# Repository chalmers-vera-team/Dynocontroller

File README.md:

# dynocontroller
Controller PCB for dyno. 

## Hardware
PCB created in Eagle 9.3.1
It is a shield to Arduino Uno that controls the dyno. 

## Software 
Software created in PlatformIO - VS Code.

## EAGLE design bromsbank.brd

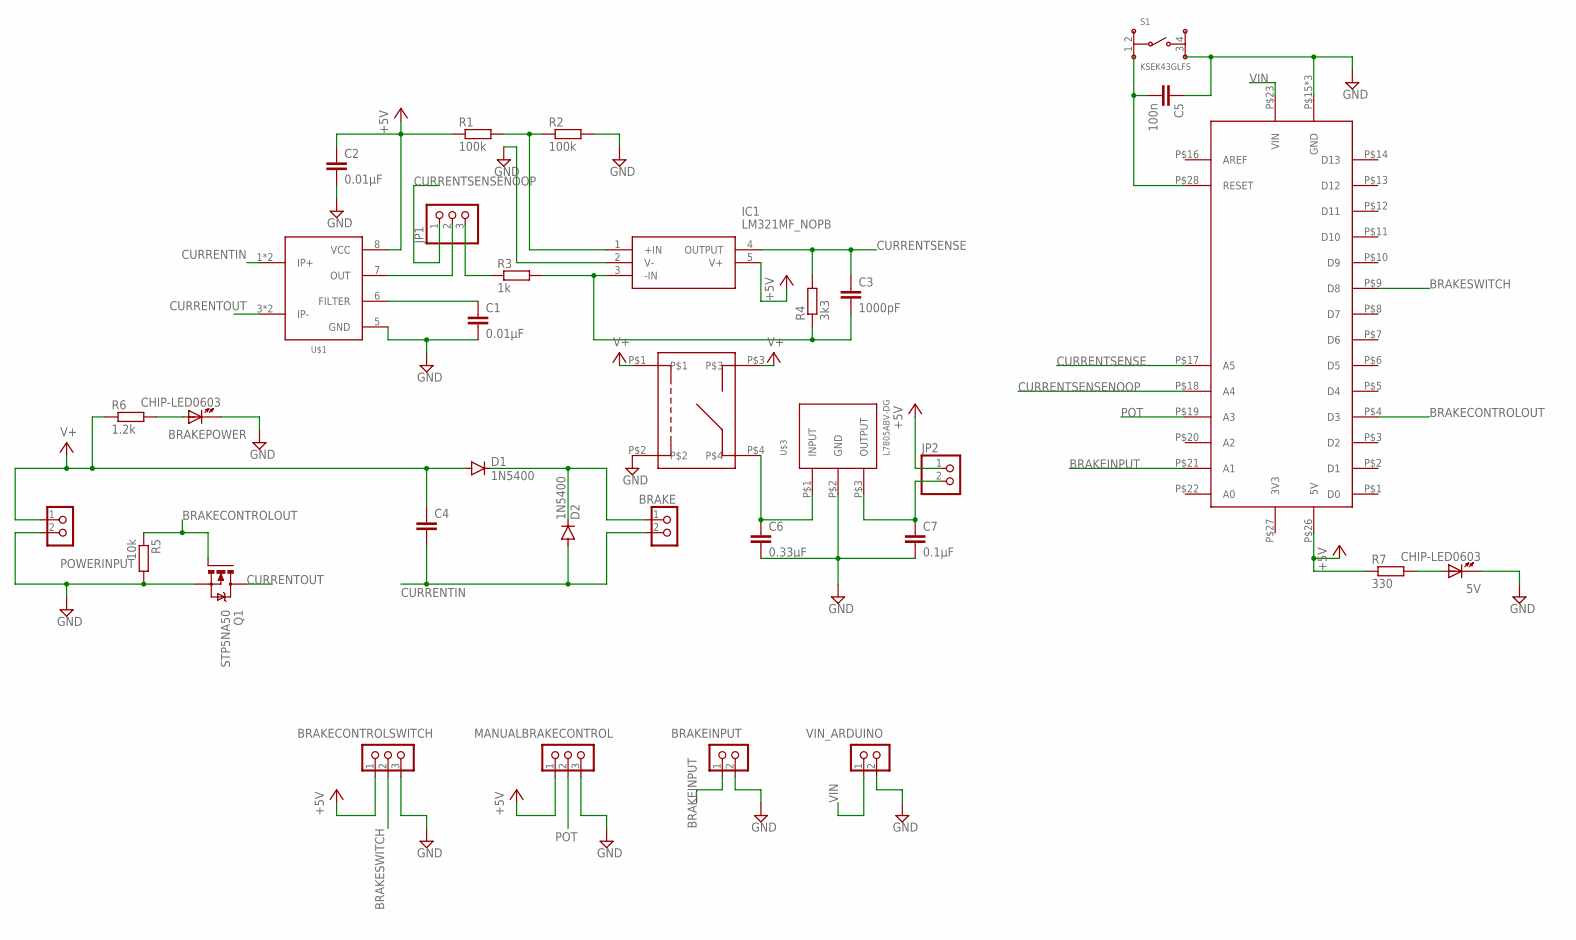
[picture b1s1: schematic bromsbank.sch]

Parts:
5V: CHIP-LED0603
BRAKE: EH_B2B-EH; B2B-EH
BRAKECONTROLSWITCH: EH_B3B-EH; B3B-EH
BRAKEINPUT: EH_B2B-EH; B2B-EH
BRAKEPOWER: CHIP-LED0603
C1, C2: 0.01µF; C0603
C3: 1000pF; C0603
C4: C-EU075-063X106; C075-063X106
C5: 100n; C0603
C6: 0.33µF; C0603
C7: 0.1µF; C0603
D1, D2: 1N5400; DO201-15
IC1: LM321MF_NOPB; SOT95P280X145-5N
JP1: PINHD-1X3; 1X03
JP2: PINHD-1X2; 1X02
MANUALBRAKECONTROL: EH_B3B-EH; B3B-EH
POWERINPUT: EH_B2B-EH; B2B-EH
Q1: STP5NA50; TO220BV
R1, R2: 100k; R0603
R3: 1k; R0603
R4: 3k3; R0603
R5: 10k; R0603
R6: 1.2k; R0603
R7: 330; R0603
S1: KSEK43GLFS
U$1: ACS712ELCTR-05B-T; SO08
U$2: ARDUINO_SHIELD; ARDUINO_UNO_SHIELD
U$3: L7805ABV-DG; TO-220
U$4: RELAY_SDT-S-124DMR,601; SDT-S-124DMR
VIN_ARDUINO: EH_B2B-EH; B2B-EH

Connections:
3V3: U$2.P$27 (3V3)
+5V: BRAKECONTROLSWITCH.1, C2.1, IC1.5 (V+), JP2.1, MANUALBRAKECONTROL.1, R1.1, R7.1, U$1.8 (VCC), U$2.P$26 (5V)
BRAKECONTROLOUT: Q1.G, R5.1, U$2.P$4 (D3)
BRAKEINPUT: BRAKEINPUT.1, U$2.P$21 (A1)
BRAKESWITCH: BRAKECONTROLSWITCH.2, U$2.P$9 (D8)
CURRENTIN: BRAKE.2, C4.2, D2.A, U$1.1 (IP+), U$1.2 (IP+)
CURRENTOUT: Q1.D, U$1.3 (IP-), U$1.4 (IP-)
CURRENTSENSE: C3.1, IC1.4 (OUTPUT), R4.2, U$2.P$17 (A5)
CURRENTSENSENOOP: JP1.1, U$2.P$18 (A4)
FILTER: C1.1, U$1.6 (FILTER)
GND: 5V.C (K), BRAKECONTROLSWITCH.3, BRAKEINPUT.2, BRAKEPOWER.C (K), C1.2, C2.2, C5.1, C6.2, C7.2, IC1.2 (V-), MANUALBRAKECONTROL.3, POWERINPUT.2, Q1.S, R2.2, R5.2, S1.3, U$1.5 (GND), U$2.P$15 (GND), U$2.P$24 (GND), U$2.P$25 (GND), U$3.P$2 (GND), U$4.P$2, VIN_ARDUINO.2
unnamed: IC1.1 (+IN), R1.2, R2.1
unnamed: BRAKEPOWER.A, R6.2
unnamed: BRAKE.1, D1.C, D2.C
unnamed: JP1.2, U$1.7 (OUT)
unnamed: C5.2, S1.1, U$2.P$28 (RESET)
unnamed: JP1.3, R3.1
unnamed: 5V.A, R7.2
unnamed: C3.2, IC1.3 (-IN), R3.2, R4.1
unnamed: C7.1, JP2.2, U$3.P$3 (OUTPUT)
unnamed: C6.1, U$3.P$1 (INPUT), U$4.P$4
POT: MANUALBRAKECONTROL.2, U$2.P$19 (A3)
V+: C4.1, D1.A, POWERINPUT.1, R6.1, U$4.P$1, U$4.P$3
VIN: U$2.P$23 (VIN), VIN_ARDUINO.1

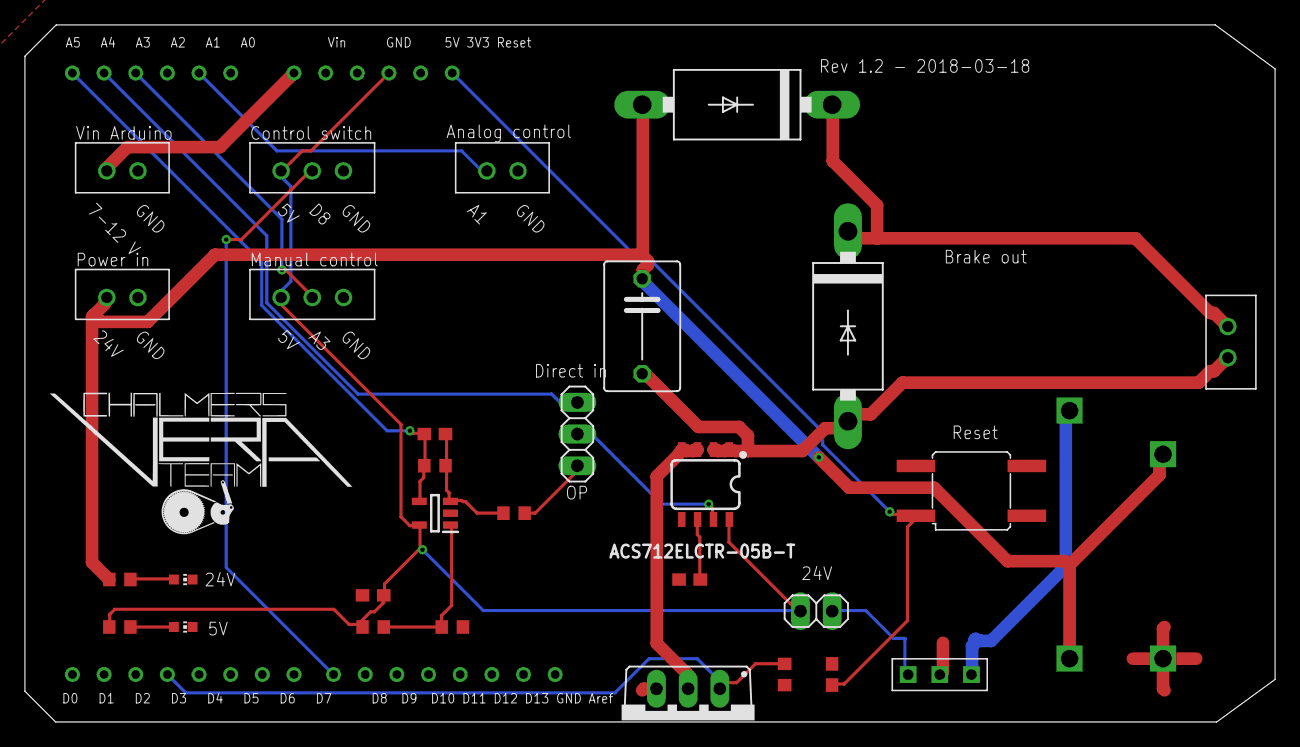
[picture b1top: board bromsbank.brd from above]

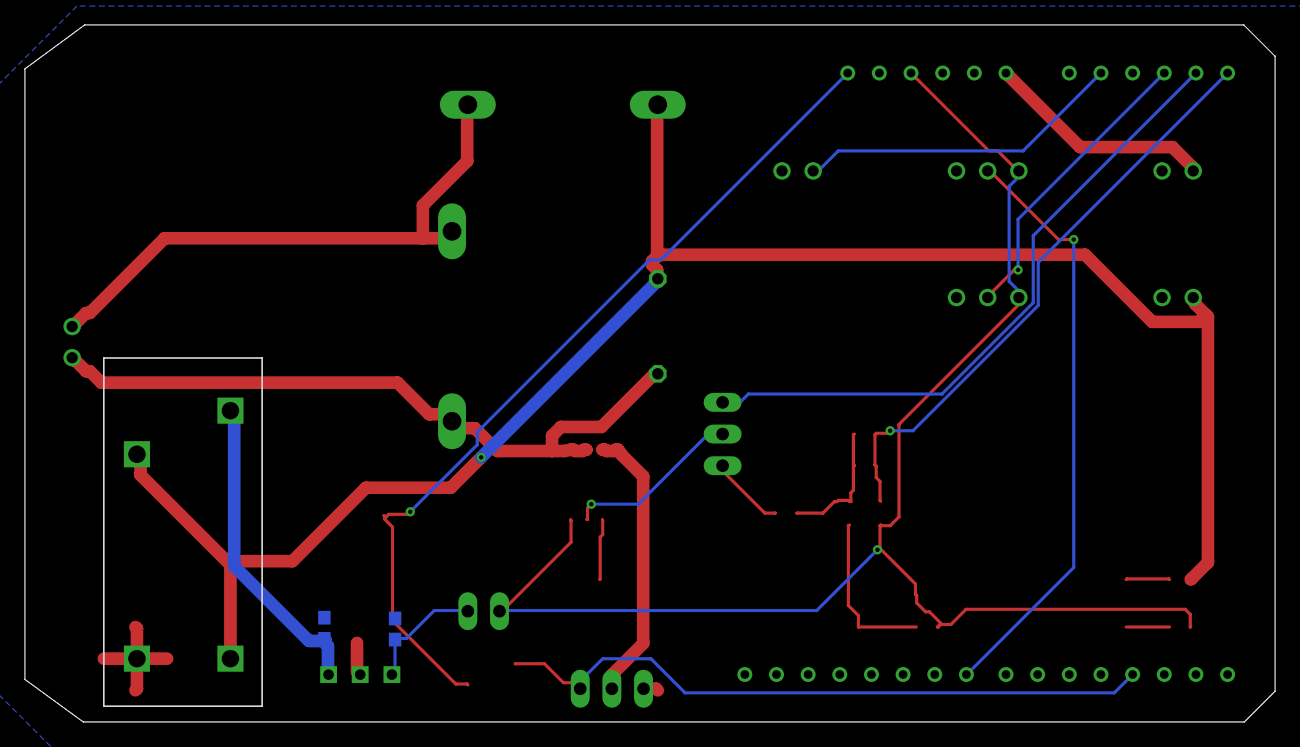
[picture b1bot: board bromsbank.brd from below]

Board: 2 copper layers, 100.3 x 55.9 mm, 33 parts (3 on the bottom side), 23 nets.

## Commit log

2019-03-21 Rev 1.2
    Schematic for PCB. Last edited 2019-03-18
2019-03-21 A little bit more informative
2019-03-21 Not verified
    This is not verified that it actually works. It should work, but I can't verify now that it is this firmware in the Arduino Uno now.
2019-03-21 Updated info and structure
    Updated info and structure. No code is changed
2019-04-16 Added Arduino project instead of VS
2019-04-16 Just moved files
2019-04-16 Updated pins, not verified
2019-04-16 Moved pinsetup to control file instead of main
2019-04-16 Create Box.ipt
    A box for putting the controller card
2019-04-16 Changed from .ino to .cpp
2019-04-16 Updated to correct input pins
    Resolves #2
2019-04-16 Update to working state
    Now it should work. Resolves #1
2019-04-26 Cleanup of old files
2019-07-15 Updated for latest hardware
2019-07-15 Added serial begin
